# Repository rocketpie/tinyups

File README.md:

# TinyUPS

like a laptop battery, but for PCs.

A compact 12 V DC UPS for mini servers fed by an external adapter and a
[picoPSU](https://en.wikipedia.org/wiki/PicoPSU) DC-ATX converter. A 4S
LiFePO₄ pack keeps the machine running when mains drops and recharges when it
returns — the whole module fits the ATX PSU bay. Battery status and a clean
shutdown signal go to the host over USB.

## Documentation

- [Design goals / requirements](docs/requirements.md)
- [Architecture](docs/architecture.md)
- [Component selection & BOM](docs/bom.md)
- [Schematic (generated)](hardware/README.md)
- [Interactive placement (browser)](ui/placement/README.md)
- [Test plan](docs/test-plan.md)
- [Toolchain status](docs/toolchain.md)
- [Decision records](docs/decisions/)

## Toolchain

Everything runs inside the dev container (see [`.devcontainer/`](.devcontainer/)).
The agent drives the tools headlessly through the [Makefile](Makefile).

| Tool | Purpose |
| --- | --- |
| KiCad 9 + `kicad-cli` | Schematic, layout, ERC, DRC, fabrication exports |
| KiBot | CI-grade automation for the checks above |
| ngspice + PySpice | Circuit simulation |
| KiUtils | Programmatic access to KiCad files |
| pytest / PyVISA / PyMeasure | Automated bring-up and acceptance tests |
| sigrok-cli | Logic analyzer captures |

Common commands:

```sh
make erc        # schematic electrical rule check
make drc        # pcb design rule check
make gerbers    # fabrication outputs
make bom        # bill of materials
make sim        # SPICE simulations
make place      # interactive placement UI (http://localhost:4097)
make route      # route a board with FreeRouting + routing/DRC report
make sense      # current-sense Kelvin check (SENSE_BOARD=<board>)
make check      # everything above (used by CI)
```

## Development container

The container installs the full EDA toolchain at build time.
For a GUI KiCad session in the browser, enable the commented
`desktop-lite` feature in `.devcontainer/devcontainer.json` (noVNC).

## Dev Container Setup, Syncing

dev container setup for use with opencode. 
git interaction from host only.

1. say you clone all your repos here:  
`~/workspaces/your-github-slug/repo-name`

2. make another copy where you want your dev containers to live:  
`~/workspaces/containers/repo-name`  
and `rm -rf ~/workspaces/containers/repo-name/.git`  
(`import.sh` copies `.git` back in for read-only history in the container)

3. Add this to your host shell (`~/.bashrc`):

    `export GIT_WORKSPACE_ROOT=~/workspaces/your-github-slug/`

4. from `~/workspaces/containers/repo-name`, run:

|command|what it does|
|---|---|
| `devcontainer up` | build and run the dev container |
| `devcontainer exec opencode pair` | start opencode in the container (open the url to connect via browser) |
| `./import.sh` | sync from GIT_WORKSPACE_ROOT/repo-name to container copy, incl. `.git/` | 
| `./export.sh` | sync from container copy to GIT_WORKSPACE_ROOT/repo-name, never `.git/` | 

Both mirror with `rsync --delete` and skip `node_modules/`. `.git/` travels
one way only: `import.sh` brings it in so the container can read the history
(`git log`, `blame`, `diff` against HEAD), `export.sh` never copies it back, so
commits still happen on the host only.

Then, you can review the changes in `~/workspaces/your-github-slug/repo-name` with VSCode or whatever floats your goat.  
And that's pretty cool!

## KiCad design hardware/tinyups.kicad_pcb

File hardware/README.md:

# Hardware

The schematic and the board are maintained as KiCad files. There is no
schematic/board generator: the board is placed and tuned by hand in the
interactive [placement UI](../ui/placement/README.md), then checked with the
tools below.

## Files

| File | Role |
| --- | --- |
| `tinyups.kicad_sch` | Schematic (source of truth). |
| `tinyups.kicad_pcb` | Board (source of truth): the adopted `try5` placement. |
| `tinyups.kicad_pro` | KiCad project (netclasses, stackup, rules). |
| `tinyups.kicad_dru` | Custom design rules. |
| `sym-lib-table` | Project symbol table (standard libs + `tinyups`). |
| `libs/tinyups.kicad_sym` | Custom IC symbols (box symbols from the datasheets). |
| `blocks.py`, `power_map.py`, `power_spec.py`, `placement_spec.py` | Shared design data: block map, per-part power estimate, per-net current/voltage, placement intent (roles + limits). |

## Board

`tinyups.kicad_pcb` is the full 124-part design, 150 × 140 mm, 4 layers:

- **Stackup:** `F.Cu` (power pours + signals) / `In1.Cu` = solid GND plane /
  `In2.Cu` = signal / `B.Cu` = signal.
- **Placement:** the `try5` hand-tuned placement (see
  [`ui/placement/placements/try5.json`](../ui/placement/placements/try5.json)).
- **Power:** high-current rails are copper **pours** on `F.Cu`, not signal
  traces (ADR-0008). `hardware/pour_power.py` builds the corridors; the tracked
  board already carries them.
- **Routing:** not routed. `make route` writes the routed board under `build/`
  and never modifies the source board.

## Commands

```sh
make erc        # schematic electrical rule check
make drc        # board DRC (incl. schematic parity)
make render     # 3D PNG render
make svg        # schematic + PCB SVG for review
make route      # FreeRouting + routing/DRC report
make power      # ampacity of the narrowest segment of every power net
make channels   # can each power net be poured at its required width?
make sim        # ngspice simulations in sim/
```

`make place` starts the interactive placement UI (see
[`ui/placement/README.md`](../ui/placement/README.md)).

## Routing

KiCad has no autorouter, so routing uses **freerouting** (Java), driven by
`hardware/route.py`: export Specctra DSN → relax only the trace width to the
JLCPCB standard 5 mil (0.127 mm) floor → route → import the session into the
board → raise any necked trace back to the floor → refill zones → save.

```sh
make route
make route ROUTE_BOARD=build/layout/board.kicad_pcb
```

Two things matter for convergence:

1. **Stackup — signal layers.** Three signal layers + a solid ground is what
   lets it route at 5 mil. A dedicated power plane (VIN_SYS on `In2.Cu`) was
   tried and removed: it cost a signal layer and the router perforated it
   anyway.
2. **Rules.** 5 mil (0.127 mm), JLCPCB standard. The fine-pitch QFN fanout is
   the only place that cannot meet it with plain traces (via-in-pad is the fix);
   `hardware/fanout.py` pre-places a radial escape for those packages.

`make drc` fails until every net is routed (unconnected pads are DRC errors).

## Power

`hardware/power_report.py` finds the **narrowest segment** of every power net
and compares its ampacity (IPC-2221, dT = 10 °C) against the net's design
current from `docs/requirements.md`/`docs/bom.md`. A signal-width trace is not a
power trace.

`hardware/power_channel.py` is the placement-side gate: a pour is ~10 mm of
copper for 20 A on 2 oz, so the placement has to leave that channel between a
net's pads. `make channels` reports it per rail.

```sh
make power
make channels
```

`hardware/routing_report.py` measures the *route*: track/via counts, per-layer
usage, minimum trace width vs the fab rule, completion, and inter-block nets.

## Status

ERC is clean. The board is placed (courtyard-clean) and poured, but **unrouted**
and the power/ampacity gate has not yet been signed off. See
[`RESUME.md`](../RESUME.md) for the current block and
[`docs/history/`](../docs/history/) for the findings behind the power-pour and
fab-tier decisions.

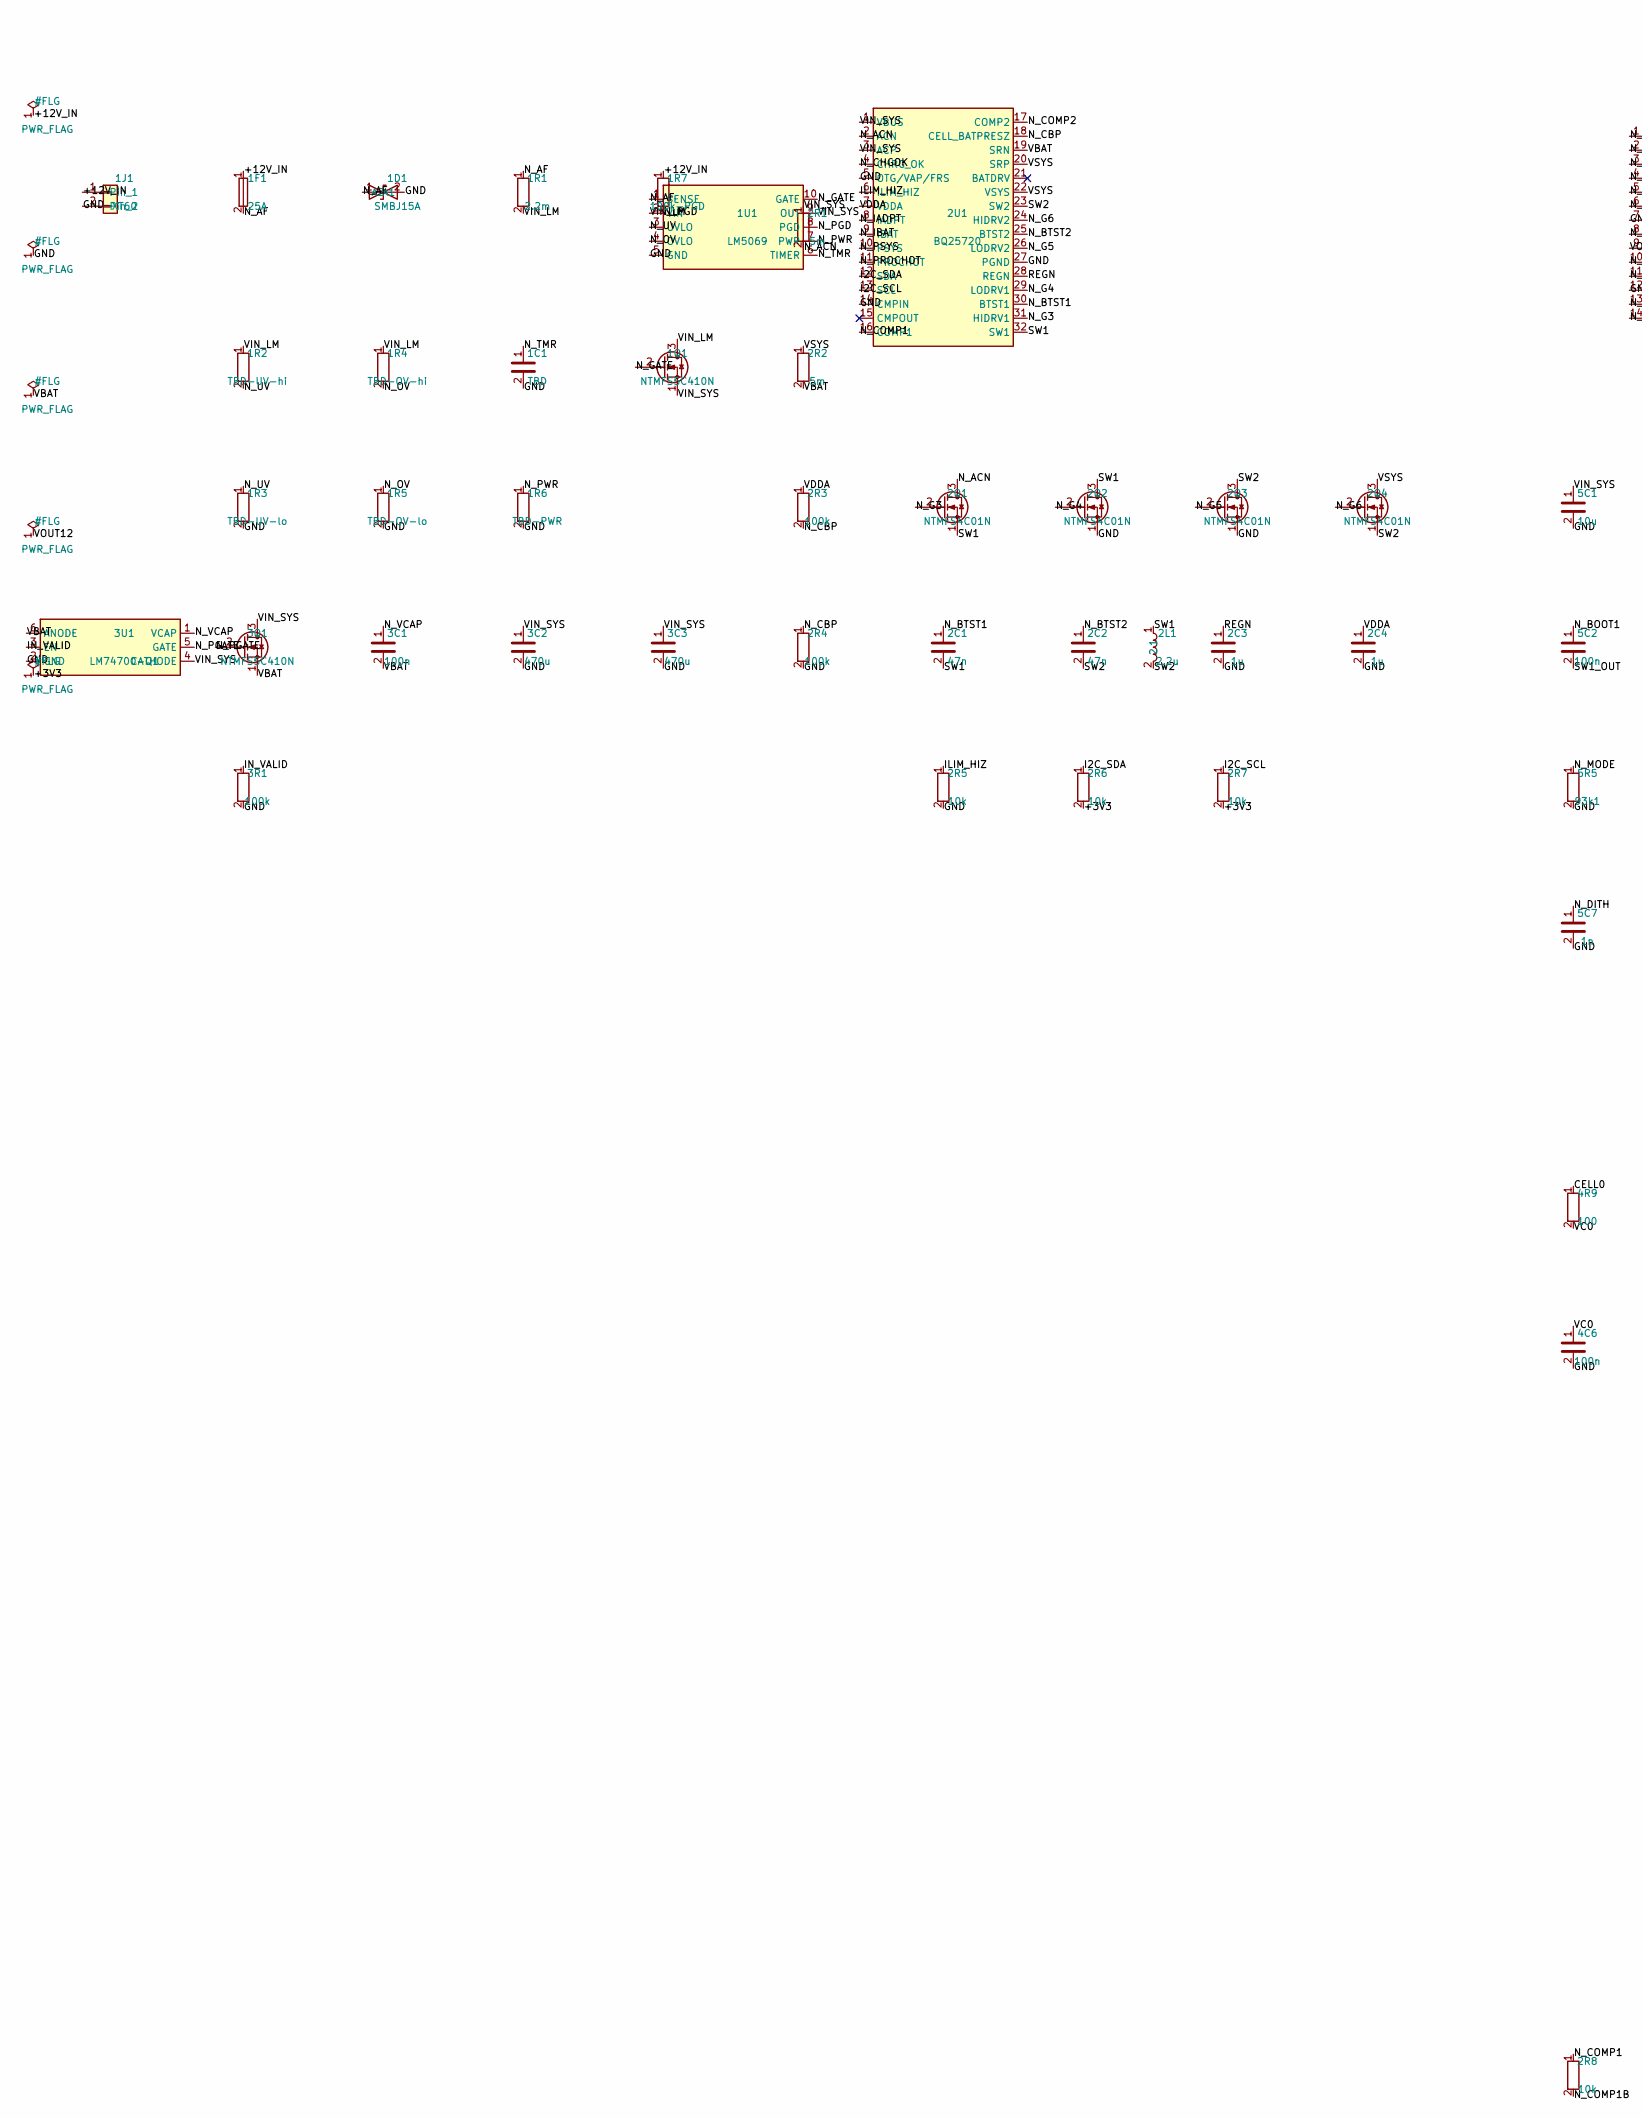
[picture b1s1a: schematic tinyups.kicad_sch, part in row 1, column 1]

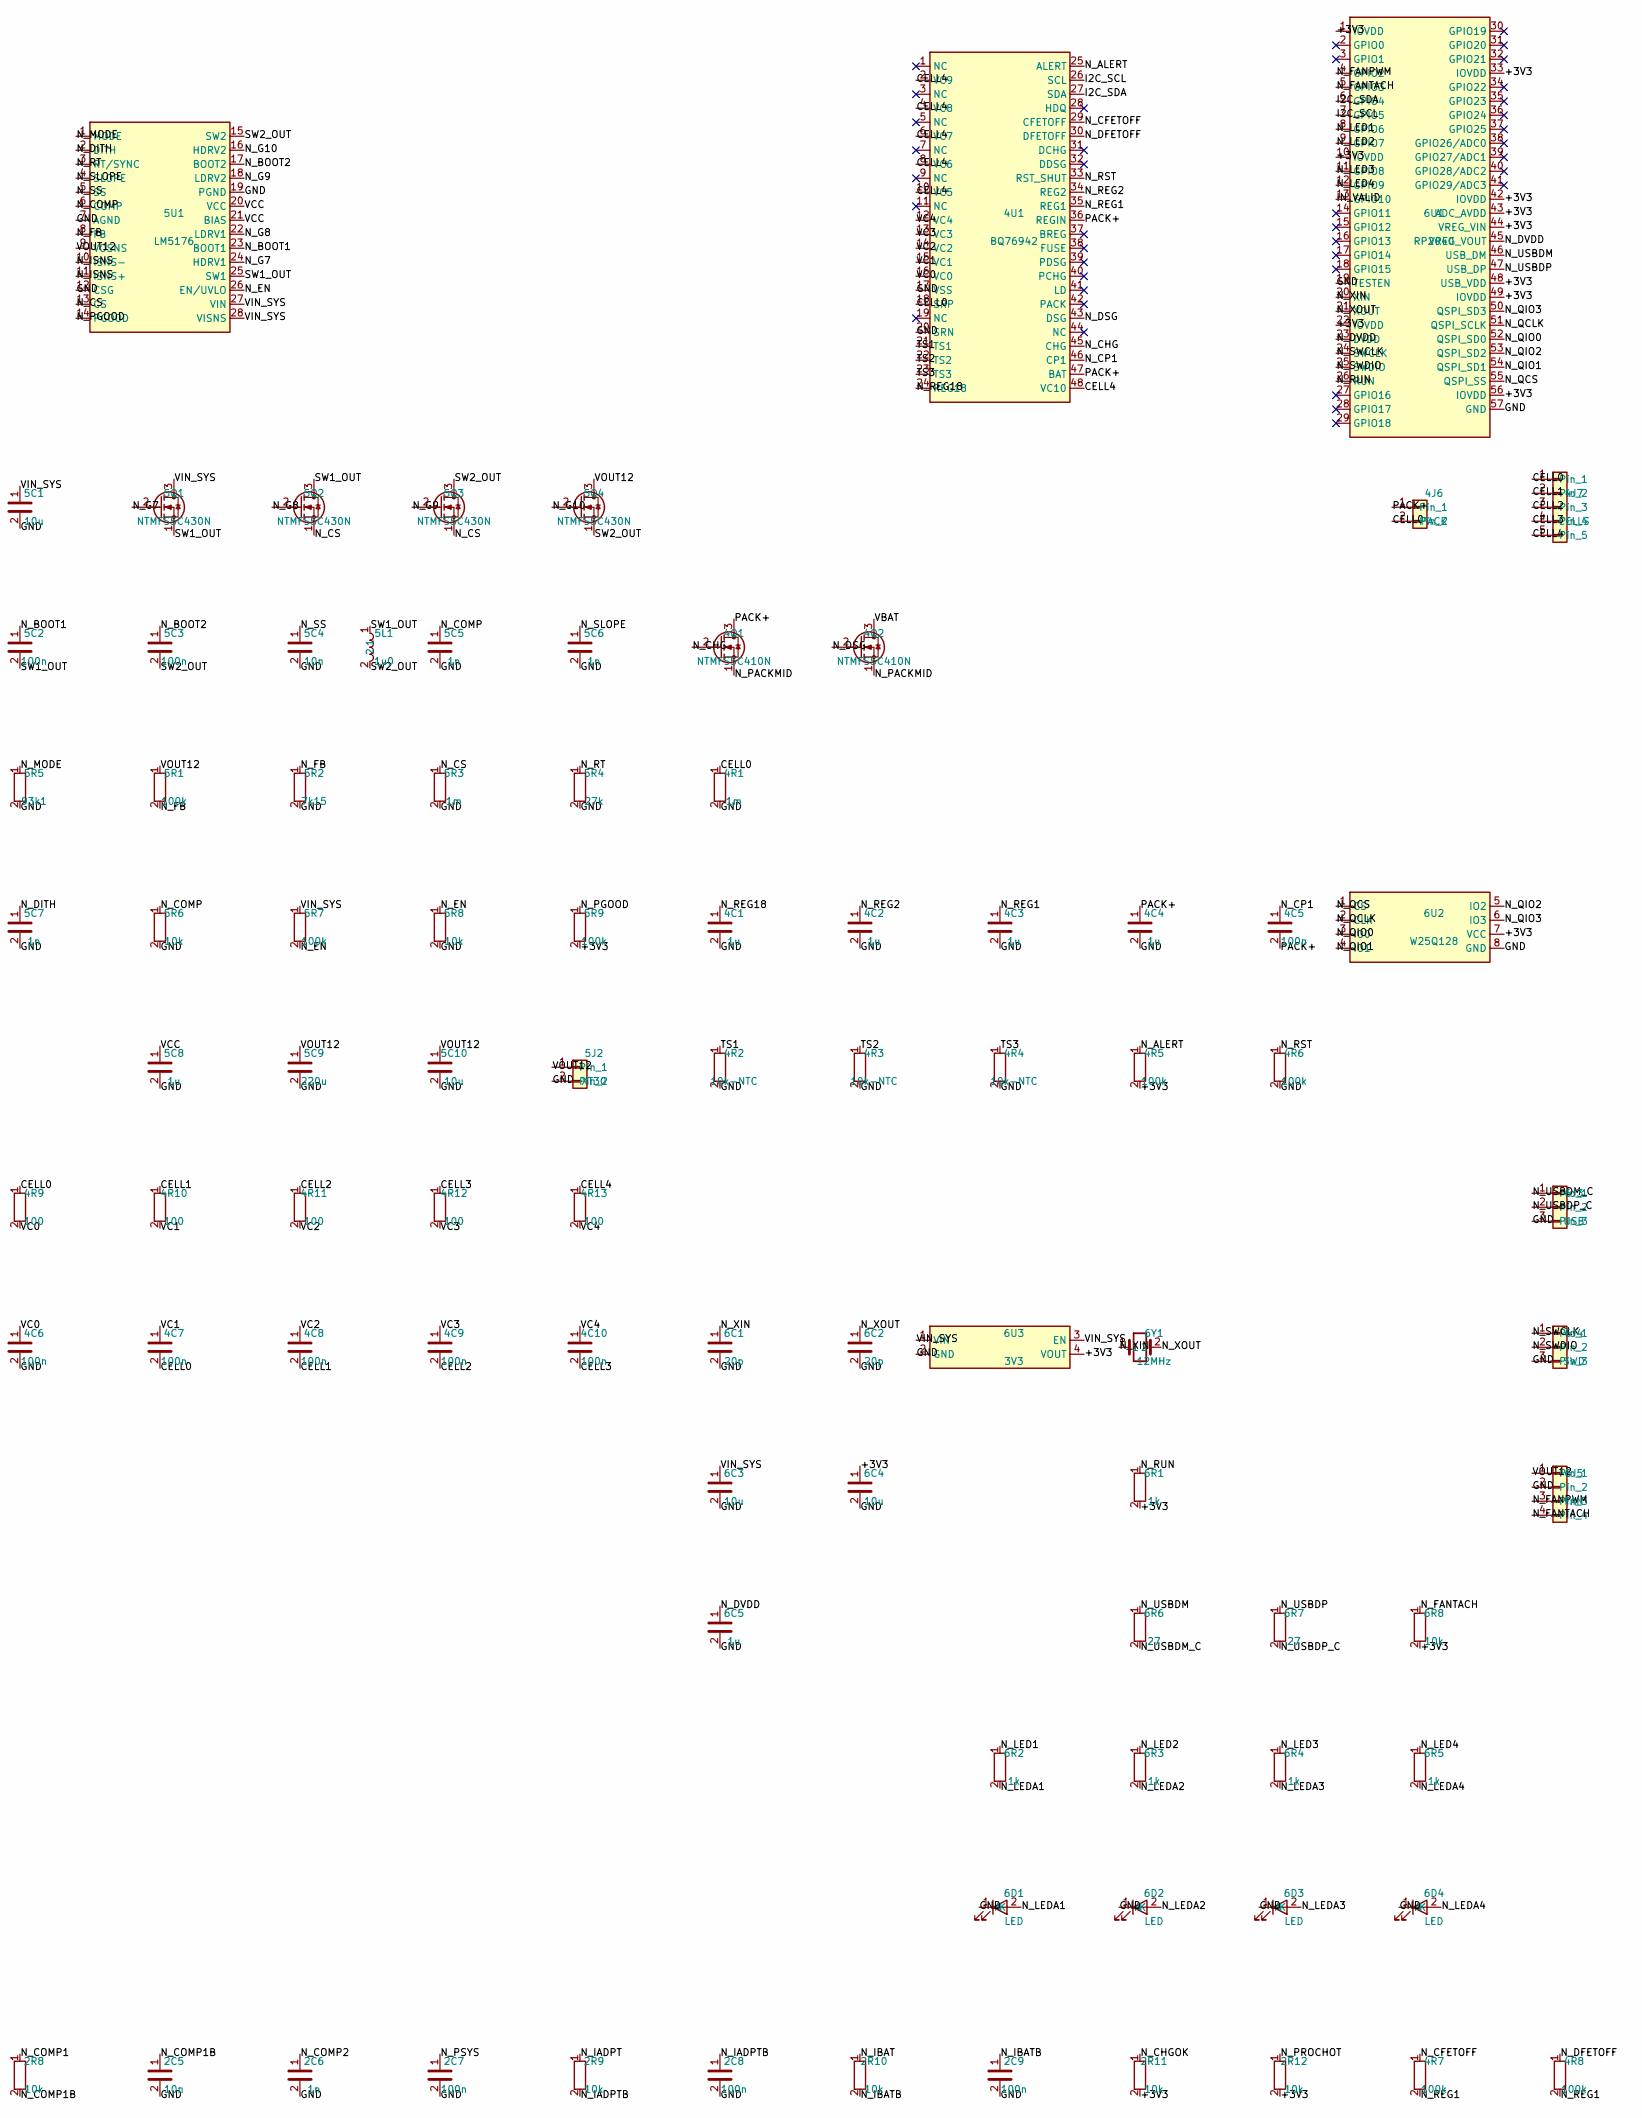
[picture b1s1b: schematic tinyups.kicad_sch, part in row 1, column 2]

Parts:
1C1: TBD; C_0805_2012Metric
1D1: SMBJ15A; D_SMB
1F1: 25A; Fuse_Blade_ATO_directSolder
1J1: XT60; SolderWire-2.5sqmm_1x02_P8.8mm_D2.4mm_OD4.4mm
1Q1, 3Q1, 4Q1, 4Q2: NTMFS5C410N; VSONP-8-1EP_5x6_P1.27mm
1R1: 2.2m; R_Shunt_Vishay_WSR2_WSR3
1R2: TBD-UV-hi; R_0805_2012Metric
1R3: TBD-UV-lo; R_0805_2012Metric
1R4: TBD-OV-hi; R_0805_2012Metric
1R5: TBD-OV-lo; R_0805_2012Metric
1R6: TBD-PWR; R_0805_2012Metric
1R7: 100k-PGD; R_0805_2012Metric
1U1: LM5069; VSSOP-10_3x3mm_P0.5mm
2C1, 2C2: 47n; C_0805_2012Metric
2C3, 2C4, 4C1, 4C2, 4C3, 4C4, 5C8, 6C5: 1u; C_0805_2012Metric
2C5, 5C4: 10n; C_0805_2012Metric
2C6, 5C5, 5C6, 5C7: 1n; C_0805_2012Metric
2C7, 2C8, 2C9, 3C1, 4C5, 4C6, 4C7, 4C8, 4C9, 4C10, 5C2, 5C3: 100n; C_0805_2012Metric
2L1: 2.2u; L_12x12mm_H8mm
2Q1, 2Q2, 2Q3, 2Q4: NTMFS4C01N; VSONP-8-1EP_5x6_P1.27mm
2R1, 2R2: 5m; R_Shunt_Vishay_WSR2_WSR3
2R3, 2R4, 3R1, 4R5, 4R6, 4R7, 4R8, 5R1, 5R7, 5R9: 100k; R_0805_2012Metric
2R5, 2R6, 2R7, 2R8, 2R9, 2R10, 2R11, 2R12, 5R6, 5R8, 6R8: 10k; R_0805_2012Metric
2U1: BQ25720; QFN-32-1EP_4x4mm_P0.4mm_EP2.65x2.65mm
3C2, 3C3: 470u; CP_Elec_8x10
3U1: LM74700-Q1; SOT-23-6
4J6: PACK; SolderWire-2.5sqmm_1x02_P8.8mm_D2.4mm_OD4.4mm
4J7: CELLS; PinHeader_1x05_P2.54mm_Vertical
4R1, 5R3: 1m; R_Shunt_Vishay_WSR2_WSR3
4R2, 4R3, 4R4: 10k-NTC; R_0805_2012Metric
4R9, 4R10, 4R11, 4R12, 4R13: 100; R_0805_2012Metric
4U1: BQ76942; TQFP-48_7x7mm_P0.5mm
5C1, 5C10, 6C3, 6C4: 10u; C_0805_2012Metric
5C9: 220u; CP_Elec_8x10
5J2: XT30; SolderWire-2.5sqmm_1x02_P7.2mm_D2.4mm_OD3.6mm
5L1: 1u0; L_12x12mm_H8mm
5Q1, 5Q2, 5Q3, 5Q4: NTMFS5C430N; VSONP-8-1EP_5x6_P1.27mm
5R2: 7k15; R_0805_2012Metric
5R4: 27k; R_0805_2012Metric
5R5: 93k1; R_0805_2012Metric
5U1: LM5176; QFN-28-1EP_4x4mm_P0.4mm_EP2.4x2.4mm
6C1, 6C2: 20p; C_0805_2012Metric
6D1, 6D2, 6D3, 6D4: LED; LED_0805_2012Metric
6J3: USB; PinHeader_1x03_P2.54mm_Vertical
6J4: SWD; PinHeader_1x03_P2.54mm_Vertical
6J5: FAN; PinHeader_1x04_P2.54mm_Vertical
6R1, 6R2, 6R3, 6R4, 6R5: 1k; R_0805_2012Metric
6R6, 6R7: 27; R_0805_2012Metric
6U1: RP2040; QFN-56-1EP_7x7mm_P0.4mm_EP3.2x3.2mm
6U2: W25Q128; SOIC-8_3.9x4.9mm_P1.27mm
6U3: 3V3; SOT-23-5
6Y1: 12MHz; Crystal_SMD_5032-2Pin_5.0x3.2mm

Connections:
/+3V3: 2R6.2, 2R7.2, 2R11.2, 2R12.2, 4R5.2, 5R9.2, 6C4.1, 6R1.2, 6R8.2, 6U1.1 (IOVDD), 6U1.10 (IOVDD), 6U1.22 (IOVDD), 6U1.33 (IOVDD), 6U1.42 (IOVDD), 6U1.43 (ADC_AVDD), 6U1.44 (VREG_VIN), 6U1.48 (USB_VDD), 6U1.49 (IOVDD), 6U1.56 (IOVDD), 6U2.7 (VCC), 6U3.4 (VOUT)
/+12V_IN: 1F1.1, 1J1.1, 1R7.1
/CELL0: 4C7.2, 4J6.2, 4J7.1, 4R1.1, 4R9.1, 4U1.18 (SRP)
/CELL1: 4C8.2, 4J7.2, 4R10.1
/CELL2: 4C9.2, 4J7.3, 4R11.1
/CELL3: 4C10.2, 4J7.4, 4R12.1
/CELL4: 4J7.5, 4R13.1, 4U1.2 (VC9), 4U1.4 (VC8), 4U1.6 (VC7), 4U1.8 (VC6), 4U1.10 (VC5), 4U1.48 (VC10)
/GND: 1C1.2, 1D1.2 (A2), 1J1.2, 1R3.2, 1R5.2, 1R6.2, 1U1.5 (GND), 2C3.2, 2C4.2, 2C5.2, 2C6.2, 2C7.2, 2C8.2, 2C9.2, 2Q2.1 (S), 2Q3.1 (S), 2R4.2, 2R5.2, 2U1.5 (OTG/VAP/FRS), 2U1.14 (CMPIN), 2U1.27 (PGND), 3C2.2, 3C3.2, 3R1.2, 3U1.2 (GND), 4C1.2, 4C2.2, 4C3.2, 4C4.2, 4C6.2, 4R1.2, 4R2.2, 4R3.2, 4R4.2, 4R6.2, 4U1.17 (VSS), 4U1.20 (SRN), 5C1.2, 5C4.2, 5C5.2, 5C6.2, 5C7.2, 5C8.2, 5C9.2, 5C10.2, 5J2.2, 5R2.2, 5R3.2, 5R4.2, 5R5.2, 5R6.2, 5R8.2, 5U1.7 (AGND), 5U1.12 (CSG), 5U1.19 (PGND), 6C1.2, 6C2.2, 6C3.2, 6C4.2, 6C5.2, 6D1.1 (K), 6D2.1 (K), 6D3.1 (K), 6D4.1 (K), 6J3.3, 6J4.3, 6J5.2, 6U1.19 (TESTEN), 6U1.57 (GND), 6U2.8 (GND), 6U3.2 (GND)
/I2C_SCL: 2R7.1, 2U1.13 (SCL), 4U1.26 (SCL), 6U1.7 (GPIO5)
/I2C_SDA: 2R6.1, 2U1.12 (SDA), 4U1.27 (SDA), 6U1.6 (GPIO4)
/ILIM_HIZ: 2R5.1, 2U1.6 (ILIM_HIZ)
/IN_VALID: 3R1.1, 3U1.3 (EN), 6U1.13 (GPIO10)
/N_ACN: 2Q1.3 (D), 2R1.2, 2U1.2 (ACN)
/N_AF: 1D1.1 (A1), 1F1.2, 1R1.1, 1U1.1 (SENSE)
/N_ALERT: 4R5.1, 4U1.25 (ALERT)
/N_BOOT1: 5C2.1, 5U1.23 (BOOT1)
/N_BOOT2: 5C3.1, 5U1.17 (BOOT2)
/N_BTST1: 2C1.1, 2U1.30 (BTST1)
/N_BTST2: 2C2.1, 2U1.25 (BTST2)
/N_CBP: 2R3.2, 2R4.1, 2U1.18 (CELL_BATPRESZ)
/N_CFETOFF: 4R7.1, 4U1.29 (CFETOFF)
/N_CHG: 4Q1.2 (G), 4U1.45 (CHG)
/N_CHGOK: 2R11.1, 2U1.4 (CHRG_OK)
/N_COMP: 5C5.1, 5R6.1, 5U1.6 (COMP)
/N_COMP1: 2R8.1, 2U1.16 (COMP1)
/N_COMP1B: 2C5.1, 2R8.2
/N_COMP2: 2C6.1, 2U1.17 (COMP2)
/N_CP1: 4C5.1, 4U1.46 (CP1)
/N_CS: 5Q2.1 (S), 5Q3.1 (S), 5R3.1, 5U1.13 (CS)
/N_DFETOFF: 4R8.1, 4U1.30 (DFETOFF)
/N_DITH: 5C7.1, 5U1.2 (DITH)
/N_DSG: 4Q2.2 (G), 4U1.43 (DSG)
/N_DVDD: 6C5.1, 6U1.23 (DVDD), 6U1.45 (VREG_VOUT)
/N_EN: 5R7.2, 5R8.1, 5U1.26 (EN/UVLO)
/N_FANPWM: 6J5.3, 6U1.4 (GPIO2)
/N_FANTACH: 6J5.4, 6R8.1, 6U1.5 (GPIO3)
/N_FB: 5R1.2, 5R2.1, 5U1.8 (FB)
/N_G3: 2Q1.2 (G), 2U1.31 (HIDRV1)
/N_G4: 2Q2.2 (G), 2U1.29 (LODRV1)
/N_G5: 2Q3.2 (G), 2U1.26 (LODRV2)
/N_G6: 2Q4.2 (G), 2U1.24 (HIDRV2)
/N_G7: 5Q1.2 (G), 5U1.24 (HDRV1)
/N_G8: 5Q2.2 (G), 5U1.22 (LDRV1)
/N_G9: 5Q3.2 (G), 5U1.18 (LDRV2)
/N_G10: 5Q4.2 (G), 5U1.16 (HDRV2)
/N_GATE: 1Q1.2 (G), 1U1.10 (GATE)
/N_IADPT: 2R9.1, 2U1.8 (IADPT)
/N_IADPTB: 2C8.1, 2R9.2
/N_IBAT: 2R10.1, 2U1.9 (IBAT)
/N_IBATB: 2C9.1, 2R10.2
/N_ISNS: 5U1.10 (ISNS-), 5U1.11 (ISNS+)
/N_LED1: 6R2.1, 6U1.8 (GPIO6)
/N_LED2: 6R3.1, 6U1.9 (GPIO7)
/N_LED3: 6R4.1, 6U1.11 (GPIO8)
/N_LED4: 6R5.1, 6U1.12 (GPIO9)
/N_LEDA1: 6D1.2 (A), 6R2.2
/N_LEDA2: 6D2.2 (A), 6R3.2
/N_LEDA3: 6D3.2 (A), 6R4.2
/N_LEDA4: 6D4.2 (A), 6R5.2
/N_MODE: 5R5.1, 5U1.1 (MODE)
/N_OV: 1R4.2, 1R5.1, 1U1.4 (OVLO)
/N_PACKMID: 4Q1.1 (S), 4Q2.1 (S)
/N_PGATE: 3Q1.2 (G), 3U1.5 (GATE)
/N_PGD: 1R7.2, 1U1.8 (PGD)
/N_PGOOD: 5R9.1, 5U1.14 (PGOOD)
/N_PROCHOT: 2R12.1, 2U1.11 (PROCHOT)
/N_PSYS: 2C7.1, 2U1.10 (PSYS)
/N_PWR: 1R6.1, 1U1.7 (PWR)
/N_QCLK: 6U1.51 (QSPI_SCLK), 6U2.2 (CLK)
/N_QCS: 6U1.55 (QSPI_SS), 6U2.1 (CS)
/N_QIO0: 6U1.52 (QSPI_SD0), 6U2.3 (IO0)
/N_QIO1: 6U1.54 (QSPI_SD1), 6U2.4 (IO1)
/N_QIO2: 6U1.53 (QSPI_SD2), 6U2.5 (IO2)
/N_QIO3: 6U1.50 (QSPI_SD3), 6U2.6 (IO3)
/N_REG1: 4C3.1, 4R7.2, 4R8.2, 4U1.35 (REG1)
/N_REG2: 4C2.1, 4U1.34 (REG2)
/N_REG18: 4C1.1, 4U1.24 (REG18)
/N_RST: 4R6.1, 4U1.33 (RST_SHUT)
/N_RT: 5R4.1, 5U1.3 (RT/SYNC)
/N_RUN: 6R1.1, 6U1.26 (RUN)
/N_SLOPE: 5C6.1, 5U1.4 (SLOPE)
/N_SS: 5C4.1, 5U1.5 (SS)
/N_SWCLK: 6J4.1, 6U1.24 (SWCLK)
/N_SWDIO: 6J4.2, 6U1.25 (SWDIO)
/N_TMR: 1C1.1, 1U1.6 (TIMER)
/N_USBDM: 6R6.1, 6U1.46 (USB_DM)
/N_USBDM_C: 6J3.1, 6R6.2
/N_USBDP: 6R7.1, 6U1.47 (USB_DP)
/N_USBDP_C: 6J3.2, 6R7.2
/N_UV: 1R2.2, 1R3.1, 1U1.3 (UVLO)
/N_VCAP: 3C1.1, 3U1.1 (VCAP)
/N_XIN: 6C1.1, 6U1.20 (XIN), 6Y1.1
/N_XOUT: 6C2.1, 6U1.21 (XOUT), 6Y1.2
/PACK+: 4C4.1, 4C5.2, 4J6.1, 4Q1.3 (D), 4U1.36 (REGIN), 4U1.47 (BAT)
/REGN: 2C3.1, 2U1.28 (REGN)
/SW1: 2C1.2, 2L1.1, 2Q1.1 (S), 2Q2.3 (D), 2U1.32 (SW1)
/SW1_OUT: 5C2.2, 5L1.1, 5Q1.1 (S), 5Q2.3 (D), 5U1.25 (SW1)
/SW2: 2C2.2, 2L1.2, 2Q3.3 (D), 2Q4.1 (S), 2U1.23 (SW2)
/SW2_OUT: 5C3.2, 5L1.2, 5Q3.3 (D), 5Q4.1 (S), 5U1.15 (SW2)
/TS1: 4R2.1, 4U1.21 (TS1)
/TS2: 4R3.1, 4U1.22 (TS2)
/TS3: 4R4.1, 4U1.23 (TS3)
/VBAT: 2R2.2, 2U1.19 (SRN), 3C1.2, 3Q1.1 (S), 3U1.6 (ANODE), 4Q2.3 (D)
/VC0: 4C6.1, 4R9.2, 4U1.16 (VC0)
/VC1: 4C7.1, 4R10.2, 4U1.15 (VC1)
/VC2: 4C8.1, 4R11.2, 4U1.14 (VC2)
/VC3: 4C9.1, 4R12.2, 4U1.13 (VC3)
/VC4: 4C10.1, 4R13.2, 4U1.12 (VC4)
/VCC: 5C8.1, 5U1.20 (VCC), 5U1.21 (BIAS)
/VDDA: 2C4.1, 2R3.1, 2U1.7 (VDDA)
/VIN_LM: 1Q1.3 (D), 1R1.2, 1R2.1, 1R4.1, 1U1.2 (VIN)
/VIN_SYS: 1Q1.1 (S), 1U1.9 (OUT), 2R1.1, 2U1.1 (VBUS), 2U1.3 (ACP), 3C2.1, 3C3.1, 3Q1.3 (D), 3U1.4 (CATHODE), 5C1.1, 5Q1.3 (D), 5R7.1, 5U1.27 (VIN), 5U1.28 (VISNS), 6C3.1, 6U3.1 (VIN), 6U3.3 (EN)
/VOUT12: 5C9.1, 5C10.1, 5J2.1, 5Q4.3 (D), 5R1.1, 5U1.9 (VOSNS), 6J5.1
/VSYS: 2Q4.3 (D), 2R2.1, 2U1.20 (SRP), 2U1.22 (VSYS)

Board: 4 copper layers, 124 parts (0 on the bottom side), 114 nets, no tracks yet.
